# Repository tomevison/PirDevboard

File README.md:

# PygmyPossum Camera Trigger
V2
- Schematic can be viewed [here](./PygmyPossumV2_Hardware/PygmyPossumV2_Hardware.pdf)
- Updated based on STM32 architecture.
  USB Bootloader makes easier for user program modification.
- Attempt to design my own PIR circuitry

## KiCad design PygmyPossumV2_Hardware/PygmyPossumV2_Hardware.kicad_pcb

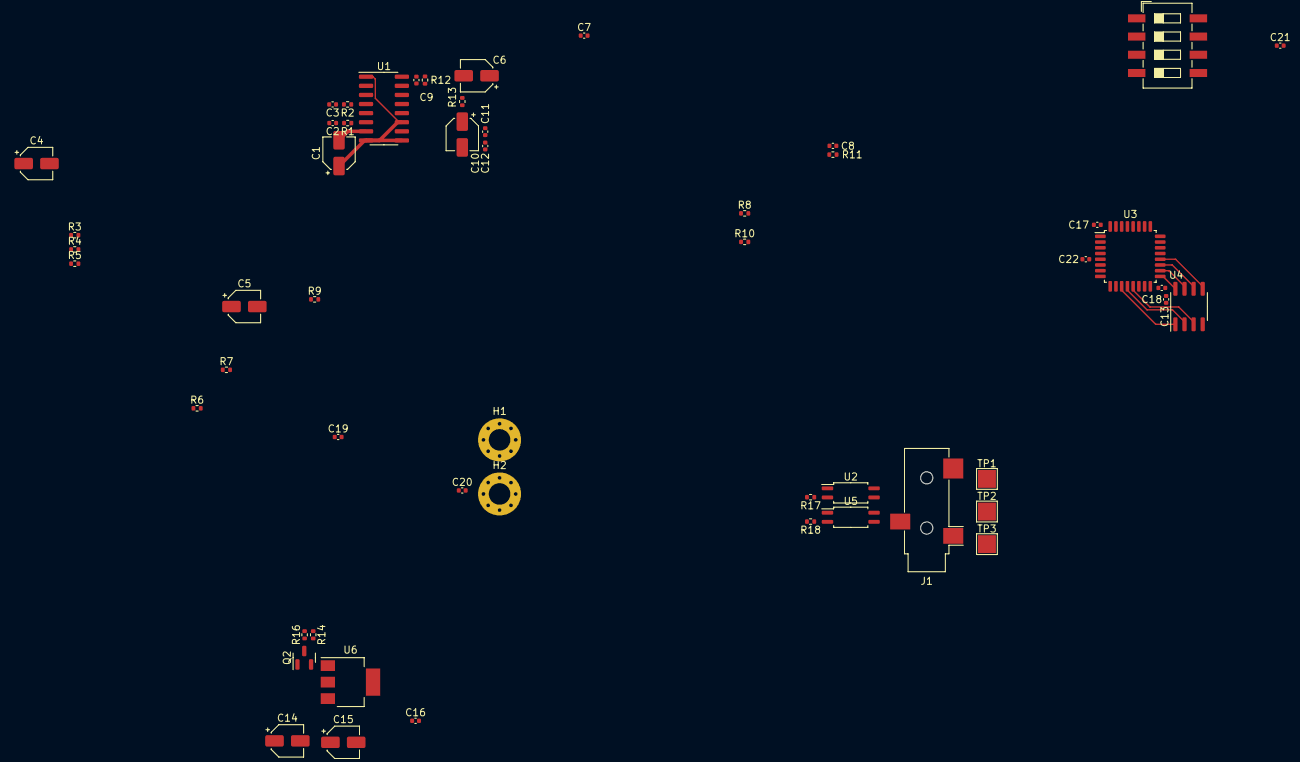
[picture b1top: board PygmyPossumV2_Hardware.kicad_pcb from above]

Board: 2 copper layers, 53 parts (0 on the bottom side), 44 nets.

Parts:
C1, C6: 22u; CP_Elec_4x5.4
C2, C8, C9, C12, C17, C18, C19, C20, C21, C22: 100n; C_0402_1005Metric
C3, C7, C13: 10n; C_0402_1005Metric
C4, C10: 47u; CP_Elec_4x5.4
C5: 10n; CP_Elec_4x5.4
C11: 5n; C_0402_1005Metric
C14, C15: CP10u; CP_Elec_4x3.9
C16: 0.1uF; C_0402_1005Metric
H1, H2: MountingHole_Pad; MountingHole_3mm_Pad_Via
J1: AudioJack; Jack_3.5mm_CUI_SJ-3523-SMT_Horizontal
Q2: 2N7002; SOT-23
R1, R3: 1M; R_0402_1005Metric
R2: 5K; R_0402_1005Metric
R4, R17, R18: 1K; R_0402_1005Metric
R5: 10K; R_0402_1005Metric
R6, R8, R13: 18K; R_0402_1005Metric
R7, R14, R16: 47K; R_0402_1005Metric
R9: 470K; R_0402_1005Metric
R10: 6.8K; R_0402_1005Metric
R11, R12: 2K; R_0402_1005Metric
SW1: SW_DIP_x04; SW_DIP_SPSTx04_Slide_6.7x11.72mm_W8.61mm_P2.54mm_LowProfile
TP1: T; TestPoint_Pad_2.5x2.5mm
TP2: R; TestPoint_Pad_2.5x2.5mm
TP3: S; TestPoint_Pad_2.5x2.5mm
U1: BISS0001; SOP-16_3.9x9.9mm_P1.27mm
U2, U5: PS2501-1; SOIC-4_4.55x2.6mm_P1.27mm
U3: STM32L412KBT6; LQFP-32_7x7mm_P0.8mm
U4: M24C64-RMN6TP; SOIC-8_3.9x4.9mm_P1.27mm
U6: AMS1117-3.3; SOT-223-3_TabPin2

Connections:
+3V3: C1.1, C13.2, C15.1, C16.1, C17.1, C18.1, C22.1, R5.1, U1.1 (A), U1.8 (VRF/RESET), U1.9 (VC), U1.11 (VDD), U3.1 (VDD), U3.5 (VDDA), U3.17 (VDD), U4.8 (VCC), U6.2 (VO)
/MCU CIRCUITRY/DIP0: SW1.4, U3.27 (PB4)
/MCU CIRCUITRY/DIP1: SW1.3, U3.28 (PB5)
/MCU CIRCUITRY/DIP2: SW1.2, U3.29 (PB6)
/MCU CIRCUITRY/DIP3: SW1.1, U3.30 (PB7)
/MCU CIRCUITRY/DOUT_CAM_F: U3.3 (PC15), U5.1
/MCU CIRCUITRY/DOUT_CAM_S: U2.1, U3.2 (PC14)
ANIN_BAT+: R14.1, R16.2, U3.7 (PA1)
BOOT0: C20.1, U3.31 (PH3)
BTN1: C21.1, U3.25 (PA15)
DO_BAT_ENA: Q2.1 (G), U3.8 (PA2)
GND: C1.2, C2.2, C3.2, C4.2, C5.2, C10.2, C12.1, C13.1, C14.2, C15.2, C16.2, C17.2, C18.2, C19.2, C20.2, C21.2, C22.2, H1.1, H2.1, Q2.2 (S), R3.2, R7.2, R17.2, R18.2, SW1.5, SW1.6, SW1.7, SW1.8, U1.7 (VSS), U3.16 (VSS), U3.32 (VSS), U4.4 (VSS), U6.1 (GND)
I2C1_E0: U3.11 (PA5), U4.1 (E0)
I2C1_E1: U3.12 (PA6), U4.2 (E1)
I2C1_E2: U3.13 (PA7), U4.3 (E2)
I2C1_SCL: U3.19 (PA9), U4.6 (SCL)
I2C1_SDA: U3.20 (PA10), U4.5 (SDA)
I2C1_WP: U3.18 (PA8), U4.7 (~WC)
NRST: C19.1, U3.4 (NRST)
unnamed: C4.1, R5.2, R6.1
unnamed: C6.1, C8.1, R11.1
unnamed: C8.2, R10.1, R11.2
unnamed: C10.1, R13.1
unnamed: C11.1, C12.2
unnamed: J1.R, TP2.1, U5.4
unnamed: J1.S, TP3.1, U2.3, U5.3
unnamed: J1.T, TP1.1, U2.4
unnamed: Q2.3 (D), R16.1
unnamed: R17.1, U2.2
unnamed: R18.1, U5.2
unnamed: R8.2, U1.14 (1IN+)
unnamed: C9.2, C11.2, R12.2, R13.2, U1.15 (1IN-)
unnamed: C6.2, C9.1, R12.1, U1.16 (1OUT)
unnamed: C7.1, R9.1, R10.2, U1.13 (2IN-)
unnamed: R9.2, U1.12 (2OUT)
unnamed: R3.1, U1.10 (IB)
unnamed: C3.1, R2.2, U1.4 (RC1)
unnamed: C2.1, R1.2, U1.5 (RC2)
unnamed: R2.1, U1.3 (RR1)
unnamed: R1.1, U1.6 (RR2)
unnamed: R4.1, U1.2 (V0)
unnamed: C14.1, U6.3 (VI)
PIR_TRIG: R4.2, U3.14 (PB0)
SENSOR_OUT: C5.1, R7.1, R8.1

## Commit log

2023-05-29 init
2023-06-01 Rename project, add MCU circuitry
2023-06-01 added pdf schematic
2023-06-01 Update README.md
    relative file paths always get me..
